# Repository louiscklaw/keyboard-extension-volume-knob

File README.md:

# README.md
### media control volume knob

### references
https://blog.prusaprinters.org/3d-print-an-oversized-media-control-volume-knob-arduino-basics/

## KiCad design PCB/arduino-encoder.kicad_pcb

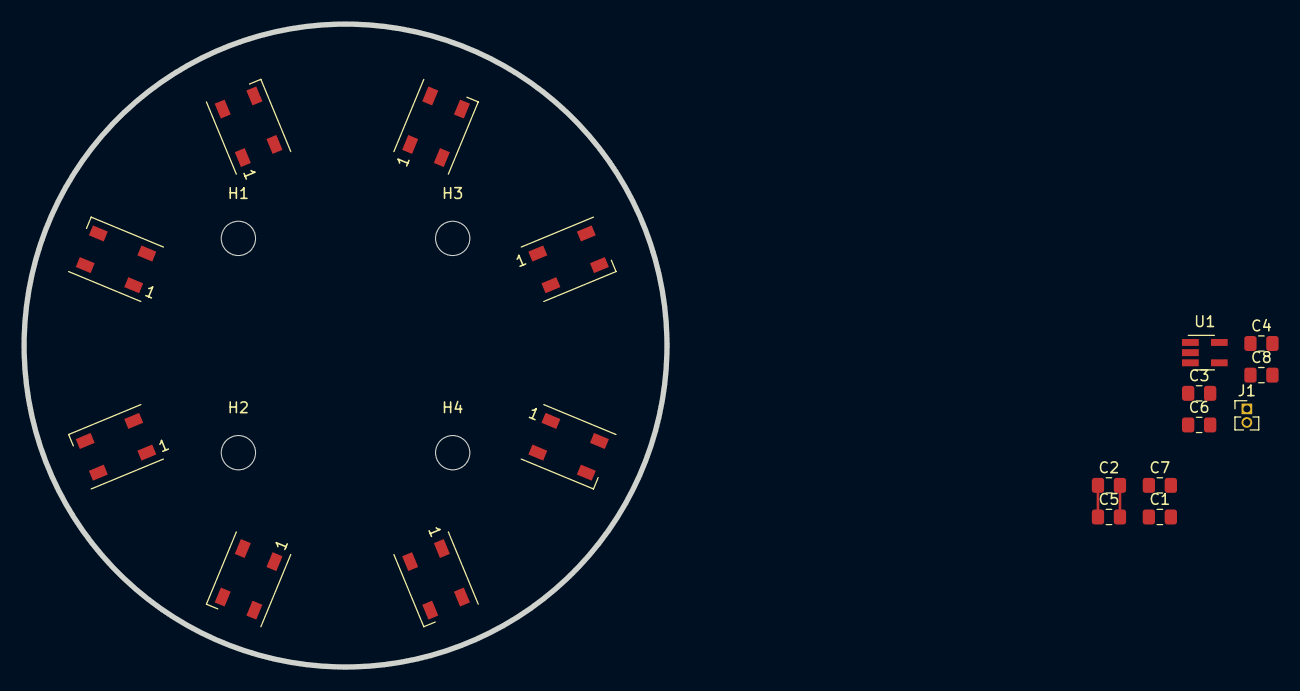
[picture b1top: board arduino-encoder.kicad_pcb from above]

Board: 2 copper layers, 60.0 x 60.0 mm, 22 parts (0 on the bottom side), 11 nets.

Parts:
C1, C2, C3, C4, C5, C6, C7, C8: C106,0805; C_0805_2012Metric_Pad1.15x1.40mm_HandSolder
D1, D2, D3, D4, D5, D6, D7, D8: WS2812B; LED_WS2812B_PLCC4_5.0x5.0mm_P3.2mm
H1, H2, H3, H4: MOUNT_M3; MountingHole_3.2mm_M3
J1: WS2812_HEADER; PinHeader_1x02_P1.27mm_Vertical
U1: 74AHCT1G125; SOT-23-5_HandSoldering

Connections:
+5V: C1.2, C2.2, C3.2, C4.2, C5.2, C6.2, C7.2, C8.2, D1.1, D2.1, D3.1, D4.1, D5.1, D6.1, D7.1, D8.1, U1.5
/ws2812.sch/WS2812_IN: J1.2, U1.2
GND: C1.1, C2.1, C3.1, C4.1, C5.1, C6.1, C7.1, C8.1, D1.3, D2.3, D3.3, D4.3, D5.3, D6.3, D7.3, D8.3, J1.1, U1.1, U1.3
unnamed: D1.2, D2.4
unnamed: D1.4, U1.4
unnamed: D2.2, D3.4
unnamed: D3.2, D4.4
unnamed: D4.2, D5.4
unnamed: D5.2, D6.4
unnamed: D6.2, D7.4
unnamed: D7.2, D8.4

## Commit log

2019-12-17 init commit,
2019-12-18 update,
2019-12-20 update for model,
2019-12-23 update for documentation,
2020-01-04 init script,
2020-01-04 add ws2812 circuit,
2020-01-04 update to ignore pycache,
2020-05-05 ci: init travis token,
2020-05-05 ci: init travis build config,
